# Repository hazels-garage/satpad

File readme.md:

# SatPad

30% ortholinear keyboard built using ergogen v3. 

## ERGOGEN V3!
I have not updated this project to use Ergogen v4 and am unlikely to do so.

## Features

- 30 key ortholinear split (10 column, 3 row)
- scroll wheel encoder with click
- OLED display

## Sponsored by PCBWay
This project was initially just to learn, but PCBWay reached out and offered to sponsor further development.  They've been awesome - great quality, fast fabrication and great customer service.  I'll definitely be using them for future projects.

<a href="https://www.pcbway.com/project/shareproject/SatPad_rev2_53e17b07.html">Order on PCBWay</a>
## Ergogen
built using my customized fork of ergogen that adds a bunch of footprints.

https://github.com/jasonhazel/ergogen/tree/jasonhazel

## Materials
* 1x ProMicro or equivalent
* 1x SSD1306 OLED Screen (optional, QMK Only)
* 30x 1N4148 SOD-123 Diodes
* 30x Kailh Choc v1
* 30x 1u Kailh Choc Keycaps
* 1x EVQWGD001 Encoder
* 1x C128955 Switch (optional)
* 1x LiPo Battery (optional)

## Firmware
QMK: https://github.com/jasonhazel/qmk_firmware/tree/hazel/satpad

ZMK: https://github.com/jasonhazel/zmk-config/tree/satpad

## Keymap

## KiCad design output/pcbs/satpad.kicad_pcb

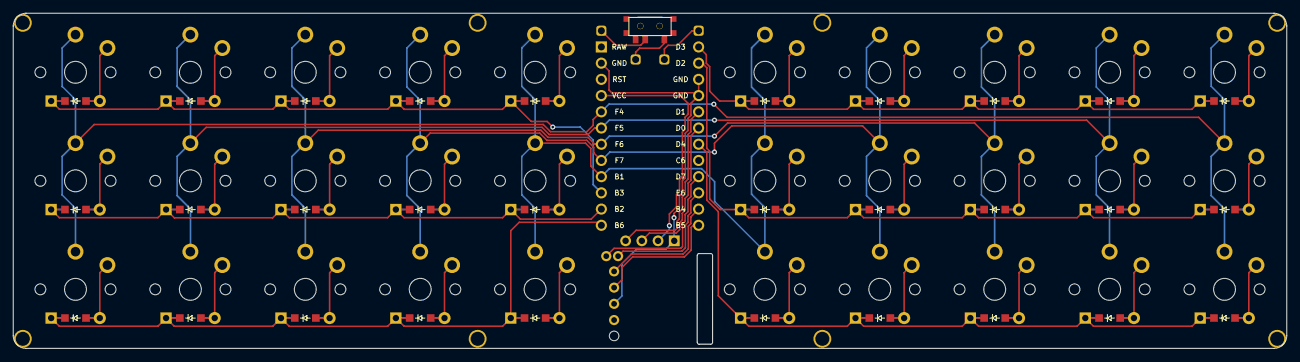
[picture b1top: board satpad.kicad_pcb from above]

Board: 2 copper layers, 199.5 x 52.5 mm, 63 parts (0 on the bottom side), 46 nets.

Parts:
D1, D2, D3, D4, D5, D6, D7, D8, D9, D10, D11, D12, D13, D14, D15, D16, D17, D18, D19, D20, D21, D22, D23, D24, D25, D26, D27, D28, D29, D30: ComboDiode
MCU1: ProMicro
OLED1: OLED; OLED_headers
S1, S2, S3, S4, S5, S6, S7, S8, S9, S10, S11, S12, S13, S14, S15, S16, S17, S18, S19, S20, S21, S22, S23, S24, S25, S26, S27, S28, S29, S30: PG1350
T1: SPDT_C128955

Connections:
B1: MCU1.9, S13.2, S14.2, S15.2, S28.2, S29.2, S30.2
B2: D2.1, D2.2, D5.1, D5.2, D8.1, D8.2, D11.1, D11.2, D14.1, D14.2, MCU1.11
B3: D3.1, D3.2, D6.1, D6.2, D9.1, D9.2, D12.1, D12.2, D15.1, D15.2, MCU1.10
B6: D1.1, D1.2, D4.1, D4.2, D7.1, D7.2, D10.1, D10.2, D13.1, D13.2, MCU1.12
Bplus: MCU1.25, T1.2
D0: MCU1.18, OLED1.3
D1: MCU1.17, OLED1.4
D2: D17.1, D17.2, D20.1, D20.2, D23.1, D23.2, D26.1, D26.2, D29.1, D29.2, MCU1.14
D3: D18.1, D18.2, D21.1, D21.2, D24.1, D24.2, D27.1, D27.2, D30.1, D30.2, MCU1.13
D4: D16.1, D16.2, D19.1, D19.2, D22.1, D22.2, D25.1, D25.2, D28.1, D28.2, MCU1.19
F4: MCU1.5, S1.2, S2.2, S3.2, S16.2, S17.2, S18.2
F5: MCU1.6, S4.2, S5.2, S6.2, S19.2, S20.2, S21.2
F6: MCU1.7, S7.2, S8.2, S9.2, S22.2, S23.2, S24.2
F7: MCU1.8, S10.2, S11.2, S12.2, S25.2, S26.2, S27.2
GND: MCU1.2, MCU1.15, MCU1.16, OLED1.1
VCC: MCU1.4, OLED1.2
index_bottom: D10.1, D10.2, S10.1
index_home: D11.1, D11.2, S11.1
index_top: D12.1, D12.2, S12.1
inner_bottom: D13.1, D13.2, S13.1
inner_home: D14.1, D14.2, S14.1
inner_top: D15.1, D15.2, S15.1
middle_bottom: D7.1, D7.2, S7.1
middle_home: D8.1, D8.2, S8.1
middle_top: D9.1, D9.2, S9.1
mirror_index_bottom: D25.1, D25.2, S25.1
mirror_index_home: D26.1, D26.2, S26.1
mirror_index_top: D27.1, D27.2, S27.1
mirror_inner_bottom: D28.1, D28.2, S28.1
mirror_inner_home: D29.1, D29.2, S29.1
mirror_inner_top: D30.1, D30.2, S30.1
mirror_middle_bottom: D22.1, D22.2, S22.1
mirror_middle_home: D23.1, D23.2, S23.1
mirror_middle_top: D24.1, D24.2, S24.1
mirror_pinky_bottom: D16.1, D16.2, S16.1
mirror_pinky_home: D17.1, D17.2, S17.1
mirror_pinky_top: D18.1, D18.2, S18.1
mirror_ring_bottom: D19.1, D19.2, S19.1
mirror_ring_home: D20.1, D20.2, S20.1
mirror_ring_top: D21.1, D21.2, S21.1
pinky_bottom: D1.1, D1.2, S1.1
pinky_home: D2.1, D2.2, S2.1
pinky_top: D3.1, D3.2, S3.1
ring_bottom: D4.1, D4.2, S4.1
ring_home: D5.1, D5.2, S5.1
ring_top: D6.1, D6.2, S6.1

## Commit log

2022-06-29 adding firmware and warning to readme
2022-06-29 show full url to firmware
2022-06-29 adding image
2022-06-29 added disclaimer about prototype
2022-06-29 adding keymap iamge
2022-06-29 fix firmware url
2022-07-05 cleanup and gerbers
2022-07-20 update picture and wip notice
2022-07-20 remove former name
2022-08-09 restructuring files
2022-08-09 add images
2022-08-10 add pcbway order link
2022-08-10 added board images
2022-08-23 add license
2022-11-10 fix qmk url
2026-03-26 Remove purchase badge from readme
    Removed purchase badge from the readme file.

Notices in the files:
readme.md:
https://img.shields.io/github/license/hazels-garage/satpad?label=%20&logo=creativecommons&logoColor=%23ffffff&style=flat-square
